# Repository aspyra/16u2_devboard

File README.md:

# 16u2_devboard
16u2 devboard, using only parts from damaged Arduino DUE boards.

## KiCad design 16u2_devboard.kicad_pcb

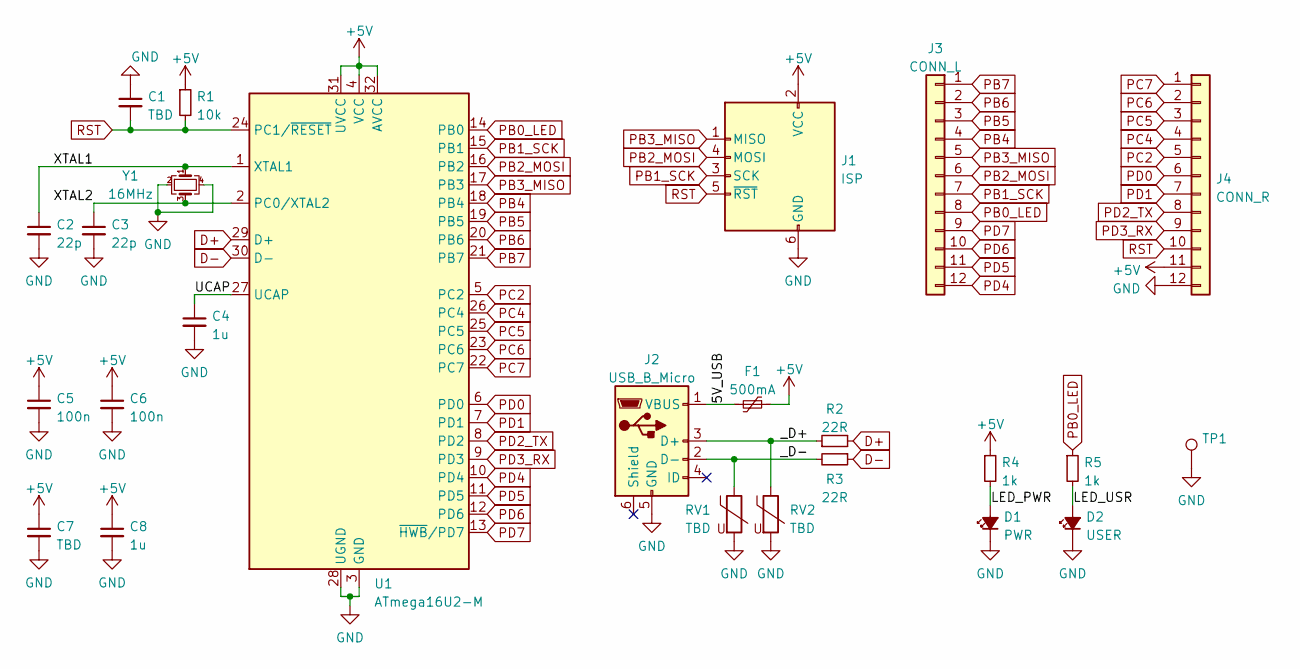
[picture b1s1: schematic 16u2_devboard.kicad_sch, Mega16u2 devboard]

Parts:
C1: TBD; C_0402_1005Metric_Pad0.74x0.62mm_HandSolder
C2, C3: 22p; C_0402_1005Metric_Pad0.74x0.62mm_HandSolder
C4, C8: 1u; C_0603_1608Metric_Pad1.08x0.95mm_HandSolder
C5, C6: 100n; C_0402_1005Metric_Pad0.74x0.62mm_HandSolder
C7: TBD; C_1210_3225Metric_Pad1.33x2.70mm_HandSolder
D1: PWR; D_0603_1608Metric_Pad1.05x0.95mm_HandSolder
D2: USER; D_0603_1608Metric_Pad1.05x0.95mm_HandSolder
F1: 500mA; Fuse_1812_4532Metric_Pad1.30x3.40mm_HandSolder
J1: ISP; PinHeader_2x03_P2.54mm_Vertical
J2: USB_B_Micro; USB_MICRO_B_C456008
J3: CONN_L; PinHeader_1x12_P2.54mm_Vertical
J4: CONN_R; PinHeader_1x12_P2.54mm_Vertical
R1: 10k; R_0402_1005Metric_Pad0.72x0.64mm_HandSolder
R2, R3: 22R; R_0402_1005Metric_Pad0.72x0.64mm_HandSolder
R4, R5: 1k; R_0402_1005Metric_Pad0.72x0.64mm_HandSolder
RV1, RV2: TBD; R_0603_1608Metric_Pad0.98x0.95mm_HandSolder
TP1: (no value)
U1: ATmega16U2-M; QFN-32-1EP_5x5mm_P0.5mm_EP3.1x3.1mm
Y1: 16MHz; Crystal_SMD_3225-4Pin_3.2x2.5mm

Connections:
+5V: C5.1, C6.1, C7.1, C8.1, F1.1, J1.2 (VCC), J4.11, R1.1, R4.1, U1.4 (VCC), U1.31 (UVCC), U1.32 (AVCC)
/5V_USB: F1.2, J2.1 (VBUS)
/LED_PWR: D1.2 (A), R4.2
/LED_USR: D2.2 (A), R5.2
/UCAP: C4.1, U1.27 (UCAP)
/XTAL1: C2.1, U1.1 (XTAL1), Y1.1
/XTAL2: C3.1, U1.2 (PC0/XTAL2), Y1.3
/_D+: J2.3 (D+), R2.1, RV2.1
/_D-: J2.2 (D-), R3.2, RV1.1
D+: R2.2, U1.29 (D+)
D-: R3.1, U1.30 (D-)
GND: C1.1, C2.2, C3.2, C4.2, C5.2, C6.2, C7.2, C8.2, D1.1 (K), D2.1 (K), J1.6 (GND), J2.5 (GND), J4.12, RV1.2, RV2.2, TP1.1, U1.3 (GND), U1.28 (UGND), U1.33 (GND), Y1.2, Y1.4
PB0_LED: J3.8, R5.1, U1.14 (PB0)
PB1_SCK: J1.3 (SCK), J3.7, U1.15 (PB1)
PB2_MOSI: J1.4 (MOSI), J3.6, U1.16 (PB2)
PB3_MISO: J1.1 (MISO), J3.5, U1.17 (PB3)
PB4: J3.4, U1.18 (PB4)
PB5: J3.3, U1.19 (PB5)
PB6: J3.2, U1.20 (PB6)
PB7: J3.1, U1.21 (PB7)
PC2: J4.5, U1.5 (PC2)
PC4: J4.4, U1.26 (PC4)
PC5: J4.3, U1.25 (PC5)
PC6: J4.2, U1.23 (PC6)
PC7: J4.1, U1.22 (PC7)
PD0: J4.6, U1.6 (PD0)
PD1: J4.7, U1.7 (PD1)
PD2_TX: J4.8, U1.8 (PD2)
PD3_RX: J4.9, U1.9 (PD3)
PD4: J3.12, U1.10 (PD4)
PD5: J3.11, U1.11 (PD5)
PD6: J3.10, U1.12 (PD6)
PD7: J3.9, U1.13 (~HWB/PD7)
RST: C1.2, J1.5 (~RST), J4.10, R1.2, U1.24 (PC1/~RESET)

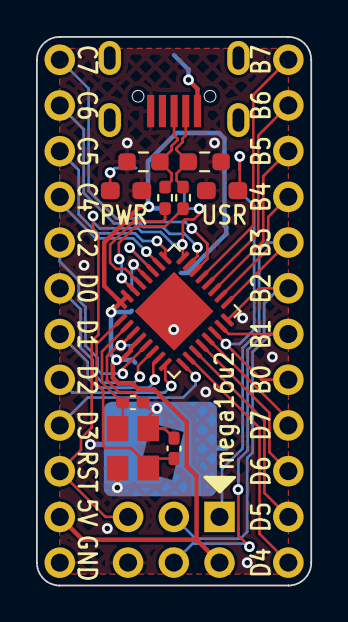
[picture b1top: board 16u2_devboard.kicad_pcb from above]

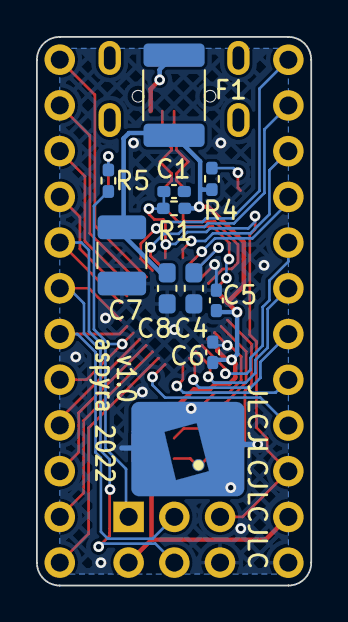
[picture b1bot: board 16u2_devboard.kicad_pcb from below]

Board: 2 copper layers, 15.2 x 30.5 mm, 25 parts (13 on the bottom side), 34 nets.

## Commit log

2022-05-21 Initial schematic created TODO: Set correct footprints
2022-05-21 Assigned footprints
2022-05-21 Loose layout created - Added netnames to schematic - Changed XTAL footprint
2022-05-21 Added backup files to .gitignore
2022-05-21 Set clearances according to JLCPCB capabilities
2022-05-21 Layout and routing in progress - removed most of front silkscreen
2022-05-22 v1.0 Finished - Layout and routing finished - Silkscreen markings added - Logo as part of ground pour
2022-05-22 Added documentation: - v1.0 schematic - v1.0 renders
2022-05-22 Generated v1.0 gerbers
2022-05-22 Fix: Added JLC order number placeholder
